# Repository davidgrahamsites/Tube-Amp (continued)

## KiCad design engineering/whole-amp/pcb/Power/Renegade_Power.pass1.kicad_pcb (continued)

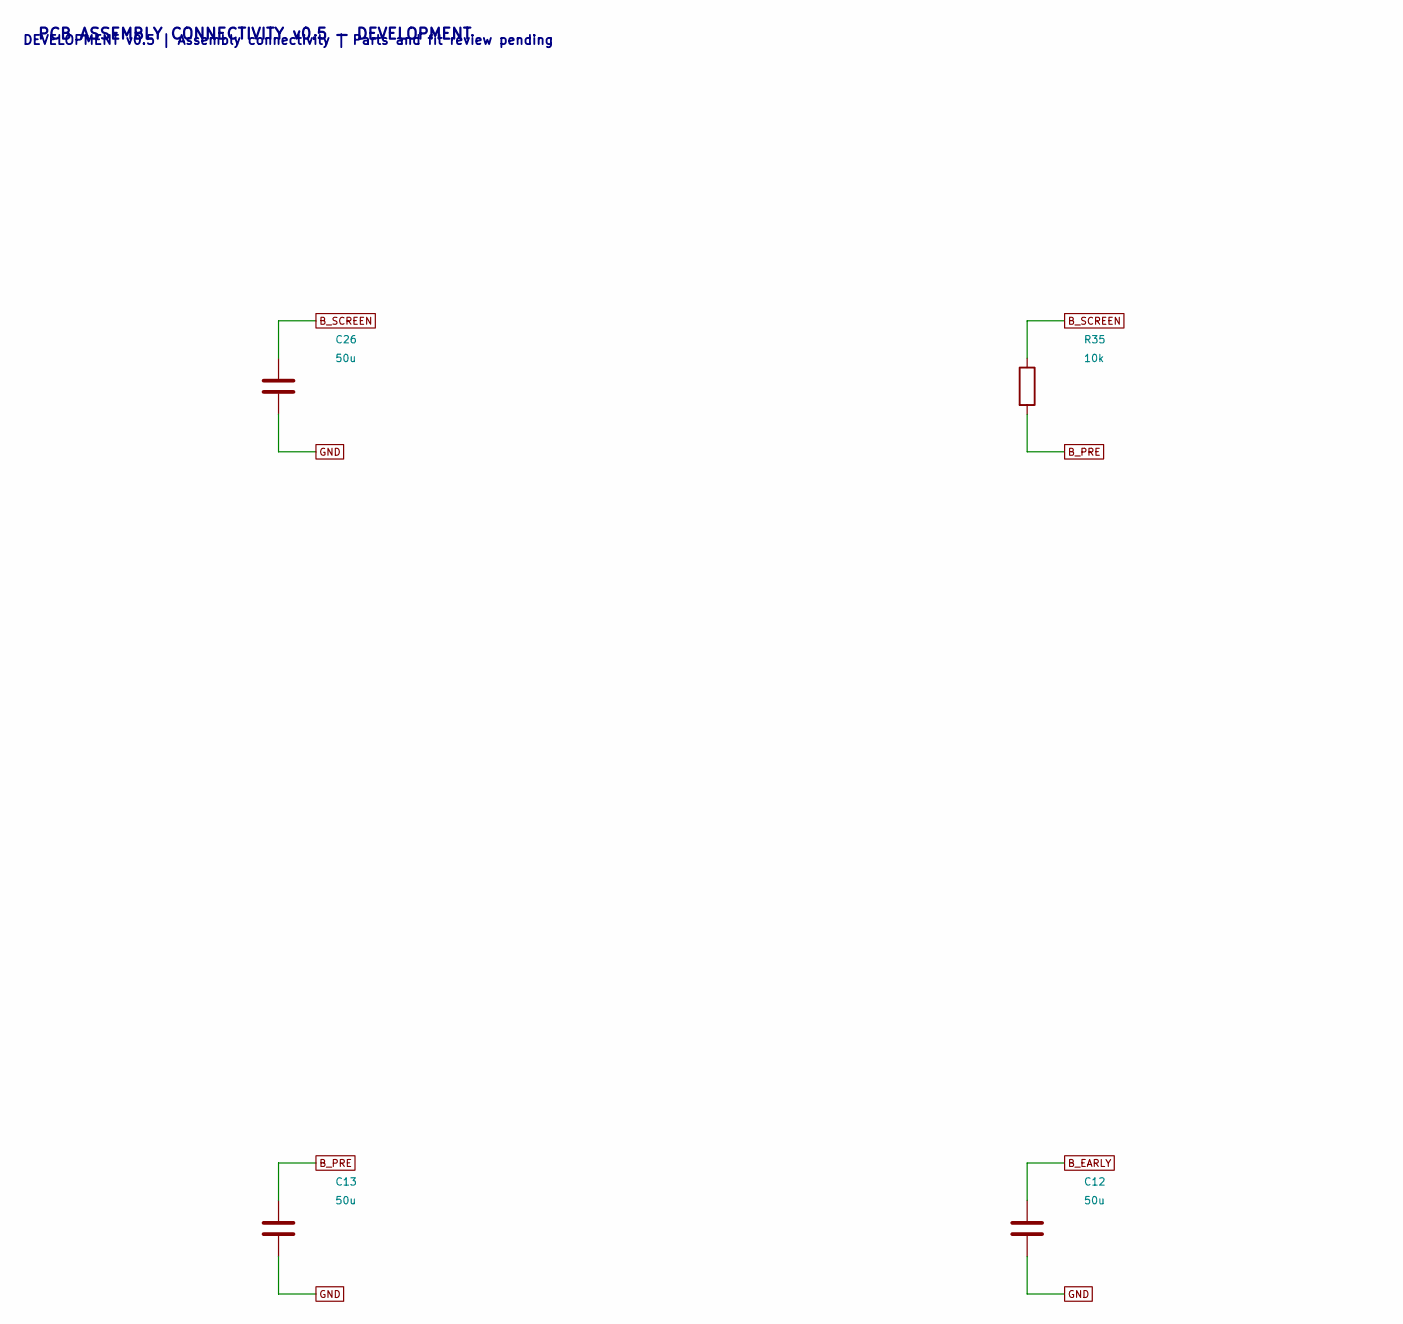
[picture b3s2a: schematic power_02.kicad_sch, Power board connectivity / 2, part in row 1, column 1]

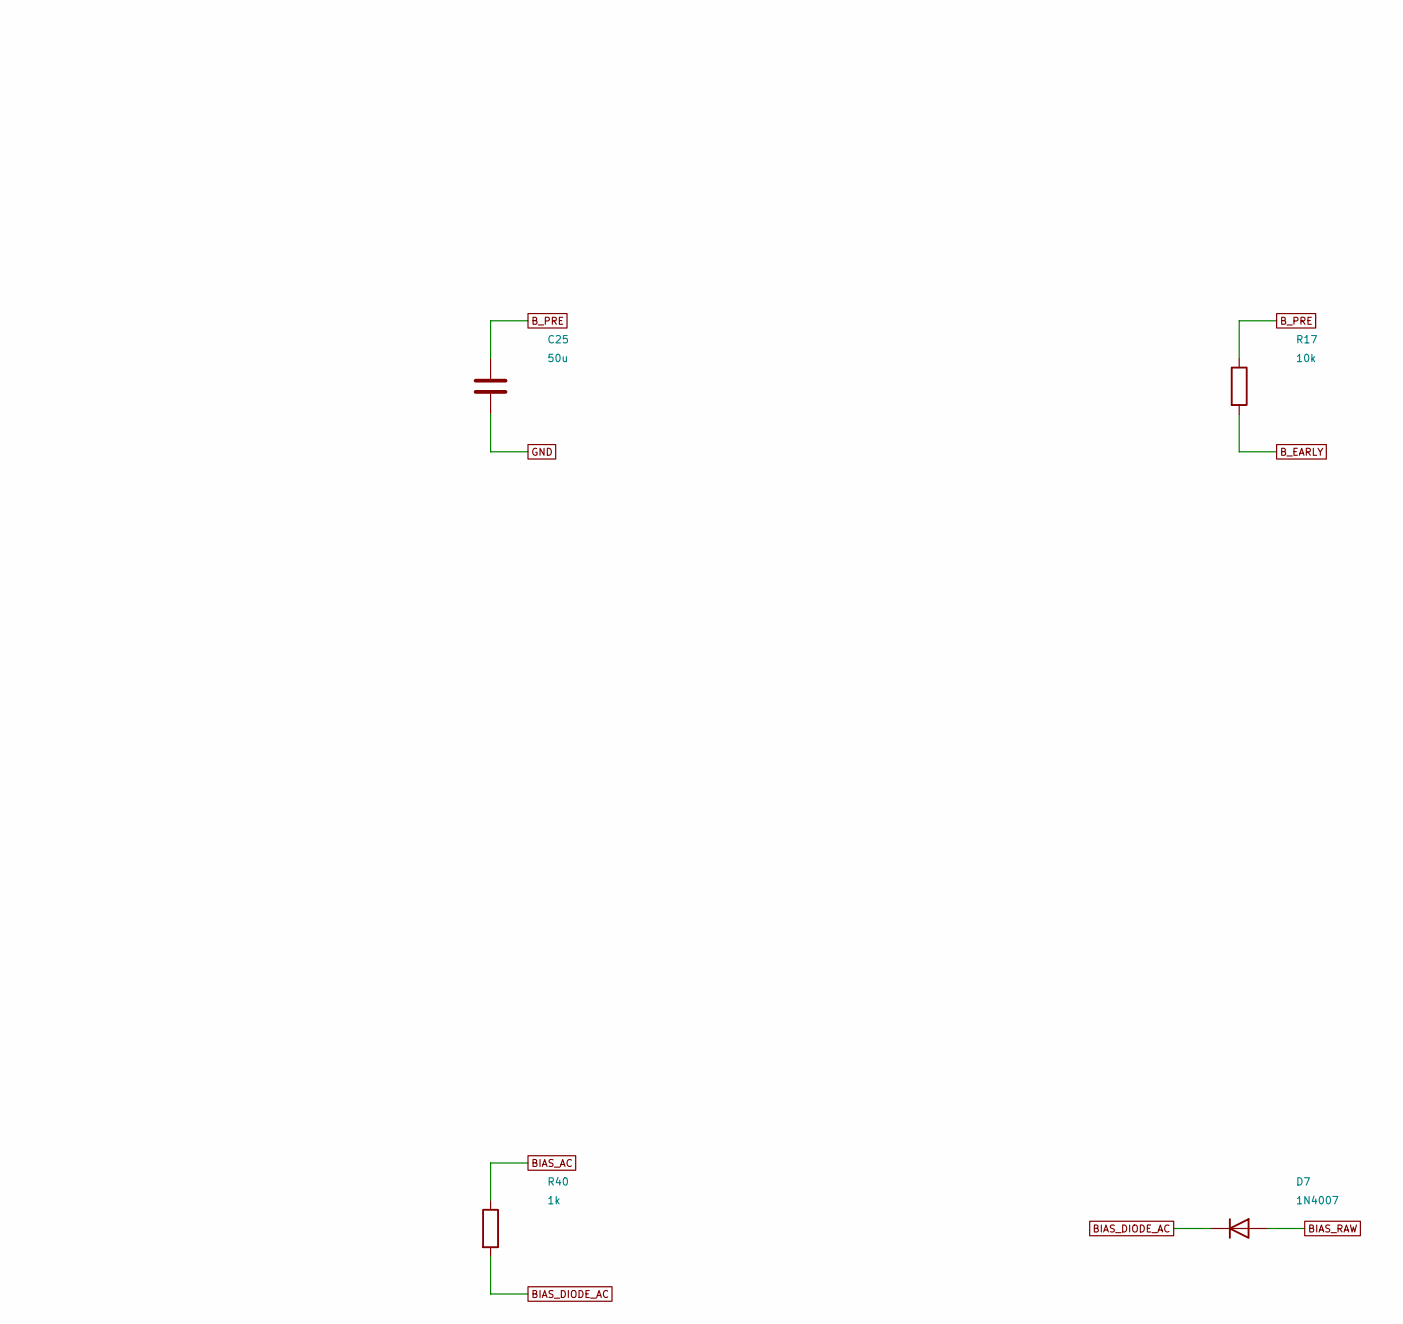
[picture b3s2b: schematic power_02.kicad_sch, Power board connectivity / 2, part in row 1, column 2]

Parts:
C12, C13, C25, C26: 50u; Panasonic_EZPV60506MTC; Rating 50uF 600VDC film; official RDL0000C251 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
D7: 1N4007; D_DO-41_SOD81_P10.16mm_Horizontal
R17, R35: 10k; R_Axial_DIN0414_L11.9mm_D4.5mm_P15.24mm_Horizontal; Rating 5 W
R40: 1k; R_Axial_DIN0207_L6.3mm_D2.5mm_P15.24mm_Horizontal; Rating 1 W

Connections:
BIAS_AC: R40.1; also elsewhere on the board
BIAS_DIODE_AC: D7.1 (K), R40.2
BIAS_RAW: D7.2 (A); also elsewhere on the board
B_EARLY: C12.1, R17.2; also elsewhere on the board
B_PRE: C13.1, C25.1, R17.1, R35.2; also elsewhere on the board
B_SCREEN: C26.1, R35.1; also elsewhere on the board
GND: C12.2, C13.2, C25.2, C26.2; also elsewhere on the board

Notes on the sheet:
PCB ASSEMBLY CONNECTIVITY v0.5 — DEVELOPMENT
DEVELOPMENT v0.5 | Assembly connectivity | Parts and fit review pending

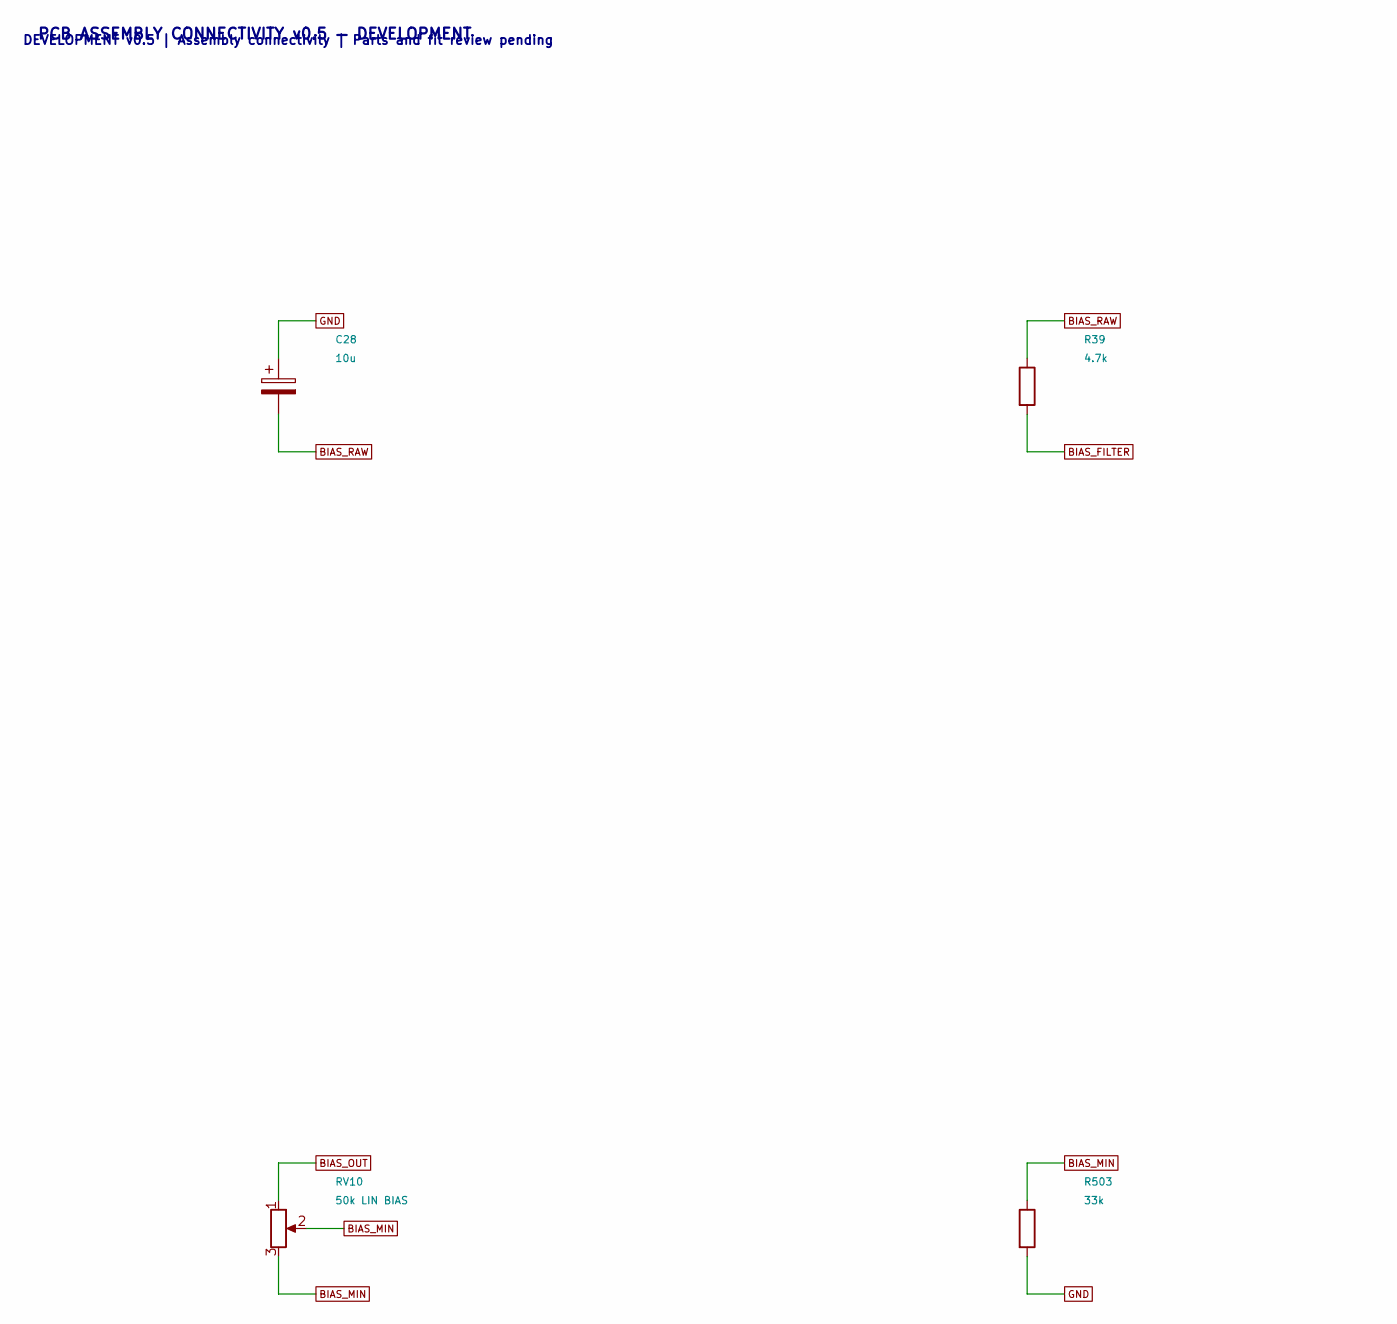
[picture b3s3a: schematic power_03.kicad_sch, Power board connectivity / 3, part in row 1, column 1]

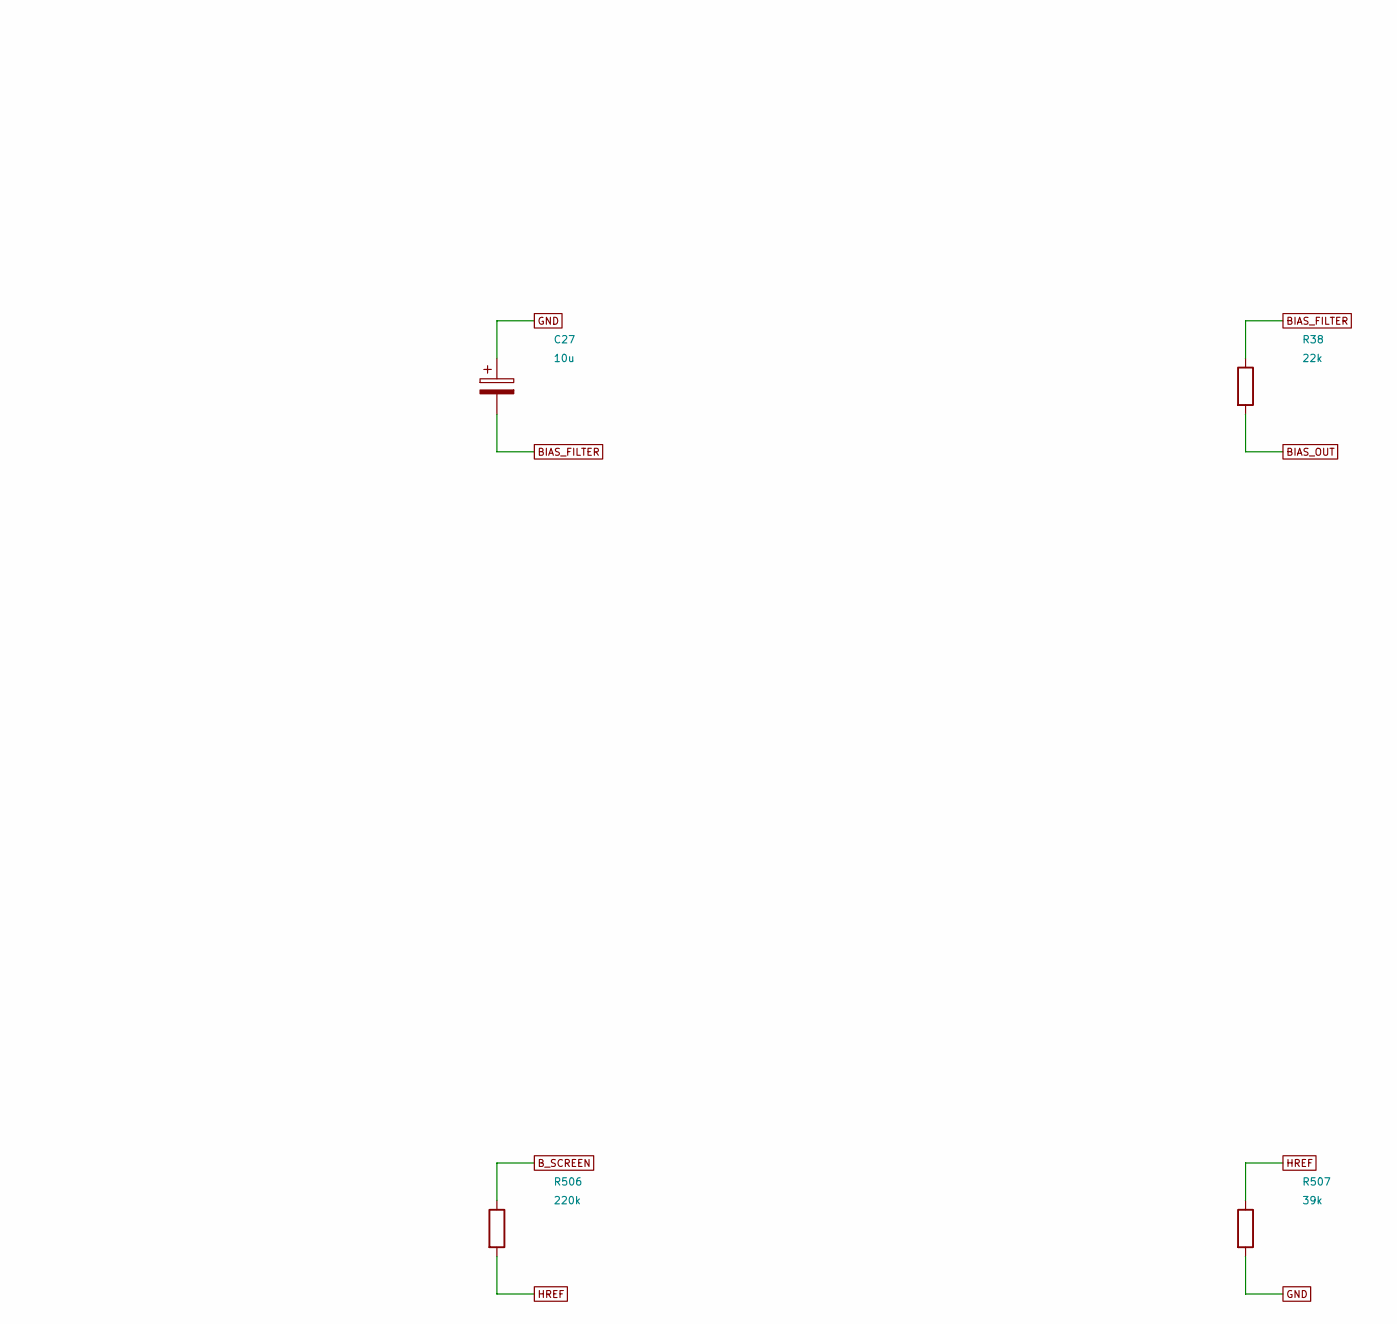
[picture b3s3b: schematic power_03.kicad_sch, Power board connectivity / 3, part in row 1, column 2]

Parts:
C27, C28: 10u; CP_Radial_D10.0mm_P5.00mm; Rating 100 V
R38: 22k; R_Axial_DIN0207_L6.3mm_D2.5mm_P15.24mm_Horizontal; Rating 1 W
R39: 4.7k; R_Axial_DIN0207_L6.3mm_D2.5mm_P15.24mm_Horizontal; Rating 1 W
R503: 33k; R_Axial_DIN0207_L6.3mm_D2.5mm_P15.24mm_Horizontal; Rating 1 W; minimum negative-bias stop
R506: 220k; R_Axial_DIN0414_L11.9mm_D4.5mm_P15.24mm_Horizontal; Rating 2 W; voltage rating pending
R507: 39k; R_Axial_DIN0207_L6.3mm_D2.5mm_P15.24mm_Horizontal; Rating 1 W
RV10: 50k LIN BIAS; Potentiometer_Bourns_3296W_Vertical; Rating Off-board; voltage, taper and drawing r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

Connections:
BIAS_FILTER: C27.2, R38.1, R39.2
BIAS_MIN: R503.1, RV10.2, RV10.3
BIAS_OUT: R38.2, RV10.1; also elsewhere on the board
BIAS_RAW: C28.2, R39.1; also elsewhere on the board
B_SCREEN: R506.1; also elsewhere on the board
GND: C27.1, C28.1, R503.2, R507.2; also elsewhere on the board
HREF: R506.2, R507.1; also elsewhere on the board

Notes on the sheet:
PCB ASSEMBLY CONNECTIVITY v0.5 — DEVELOPMENT
DEVELOPMENT v0.5 | Assembly connectivity | Parts and fit review pending

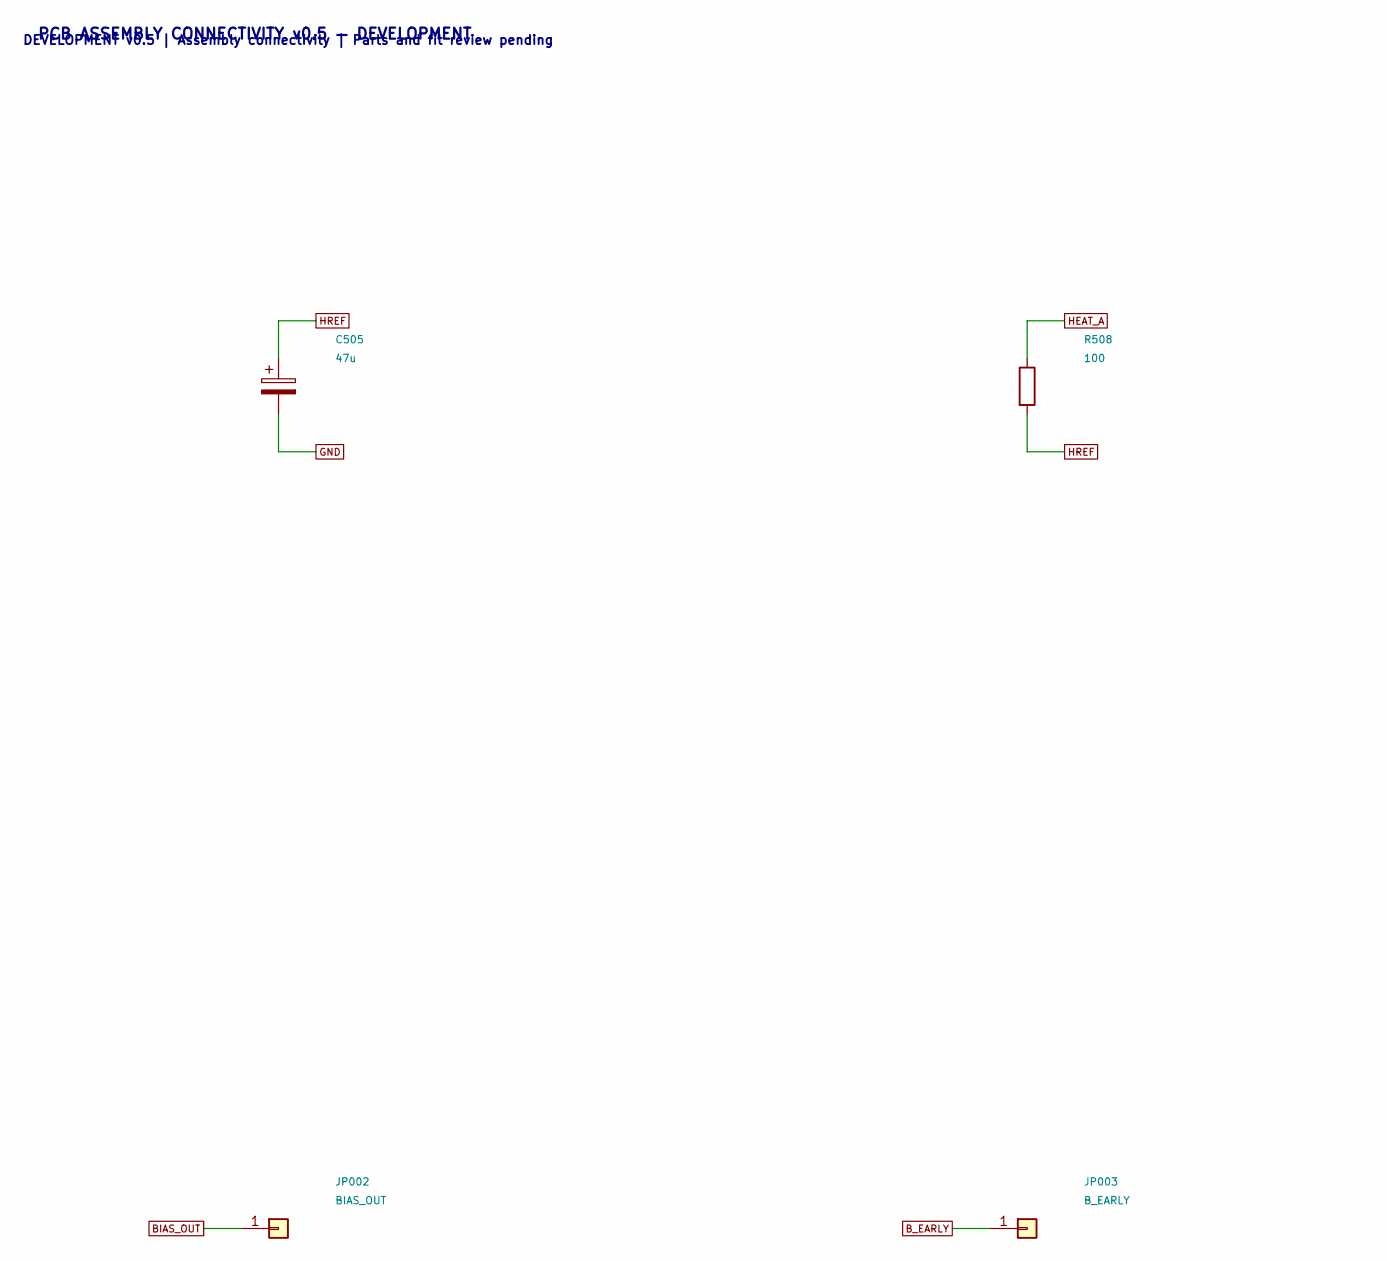
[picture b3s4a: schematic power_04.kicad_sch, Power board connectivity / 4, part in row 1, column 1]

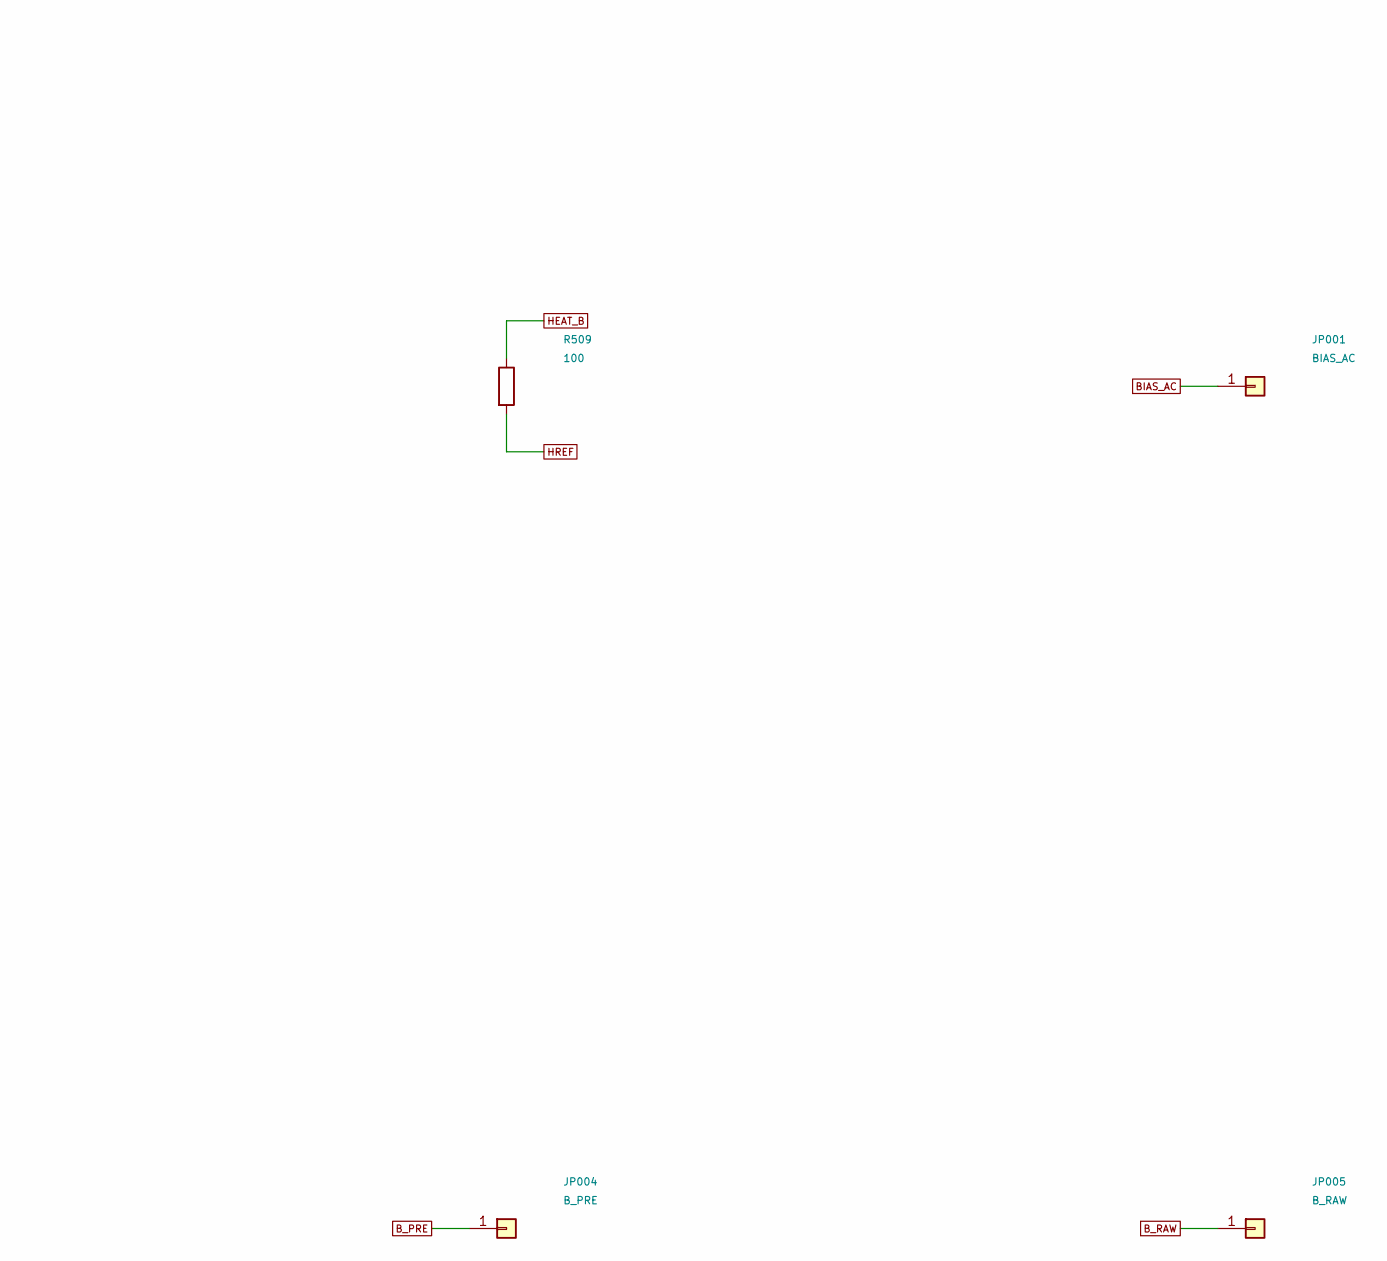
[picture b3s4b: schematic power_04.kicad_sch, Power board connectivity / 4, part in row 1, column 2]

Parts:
C505: 47u; CP_Radial_D10.0mm_P5.00mm; Rating 160 V
JP001: BIAS_AC; WirePad_1.3mm; Rating Soldered and strain-relieved wire, volt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
JP002: BIAS_OUT; WirePad_1.3mm; Rating Soldered and strain-relieved wire, volt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
JP003: B_EARLY; WirePad_1.3mm; Rating Soldered and strain-relieved wire, volt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
JP004: B_PRE; WirePad_1.3mm; Rating Soldered and strain-relieved wire, volt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
JP005: B_RAW; WirePad_1.3mm; Rating Soldered and strain-relieved wire, volt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
R508, R509: 100; R_Axial_DIN0207_L6.3mm_D2.5mm_P15.24mm_Horizontal; Rating 0.5 W

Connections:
BIAS_AC: JP001.1; also elsewhere on the board
BIAS_OUT: JP002.1; also elsewhere on the board
B_EARLY: JP003.1; also elsewhere on the board
B_PRE: JP004.1; also elsewhere on the board
B_RAW: JP005.1; also elsewhere on the board
GND: C505.2; also elsewhere on the board
HEAT_A: R508.1; also elsewhere on the board
HEAT_B: R509.1; also elsewhere on the board
HREF: C505.1, R508.2, R509.2; also elsewhere on the board

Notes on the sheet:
PCB ASSEMBLY CONNECTIVITY v0.5 — DEVELOPMENT
DEVELOPMENT v0.5 | Assembly connectivity | Parts and fit review pending

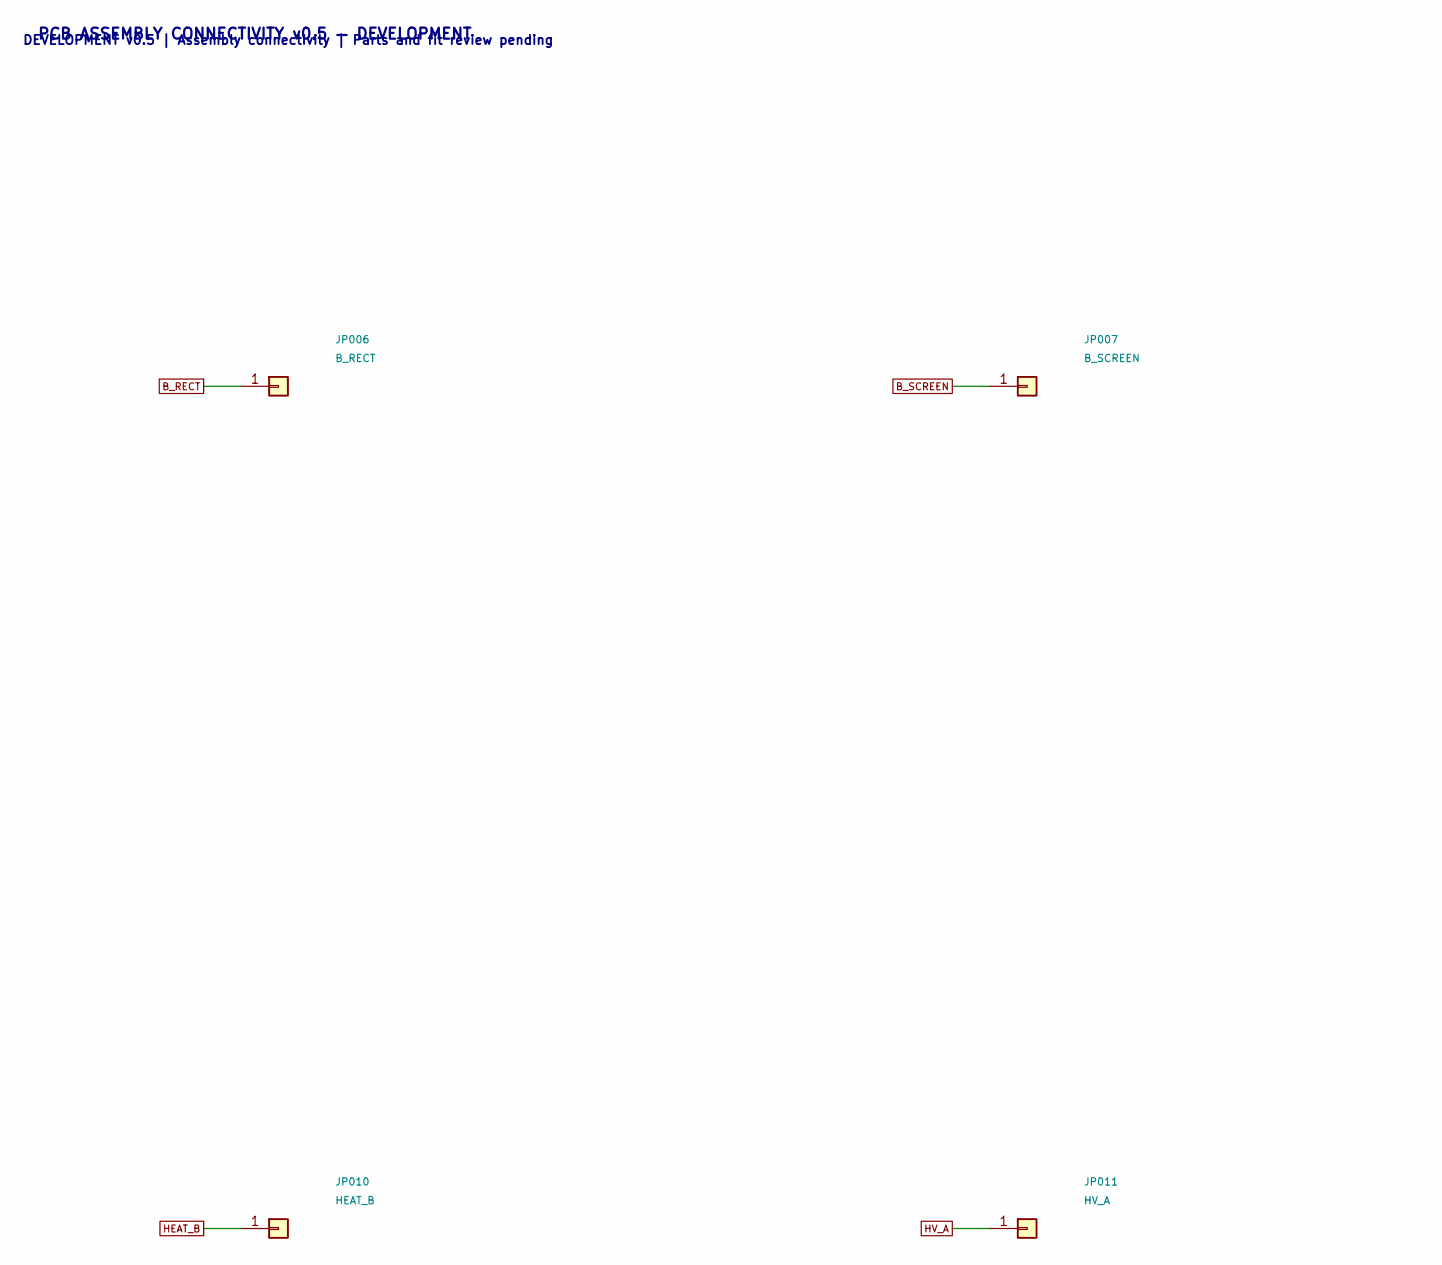
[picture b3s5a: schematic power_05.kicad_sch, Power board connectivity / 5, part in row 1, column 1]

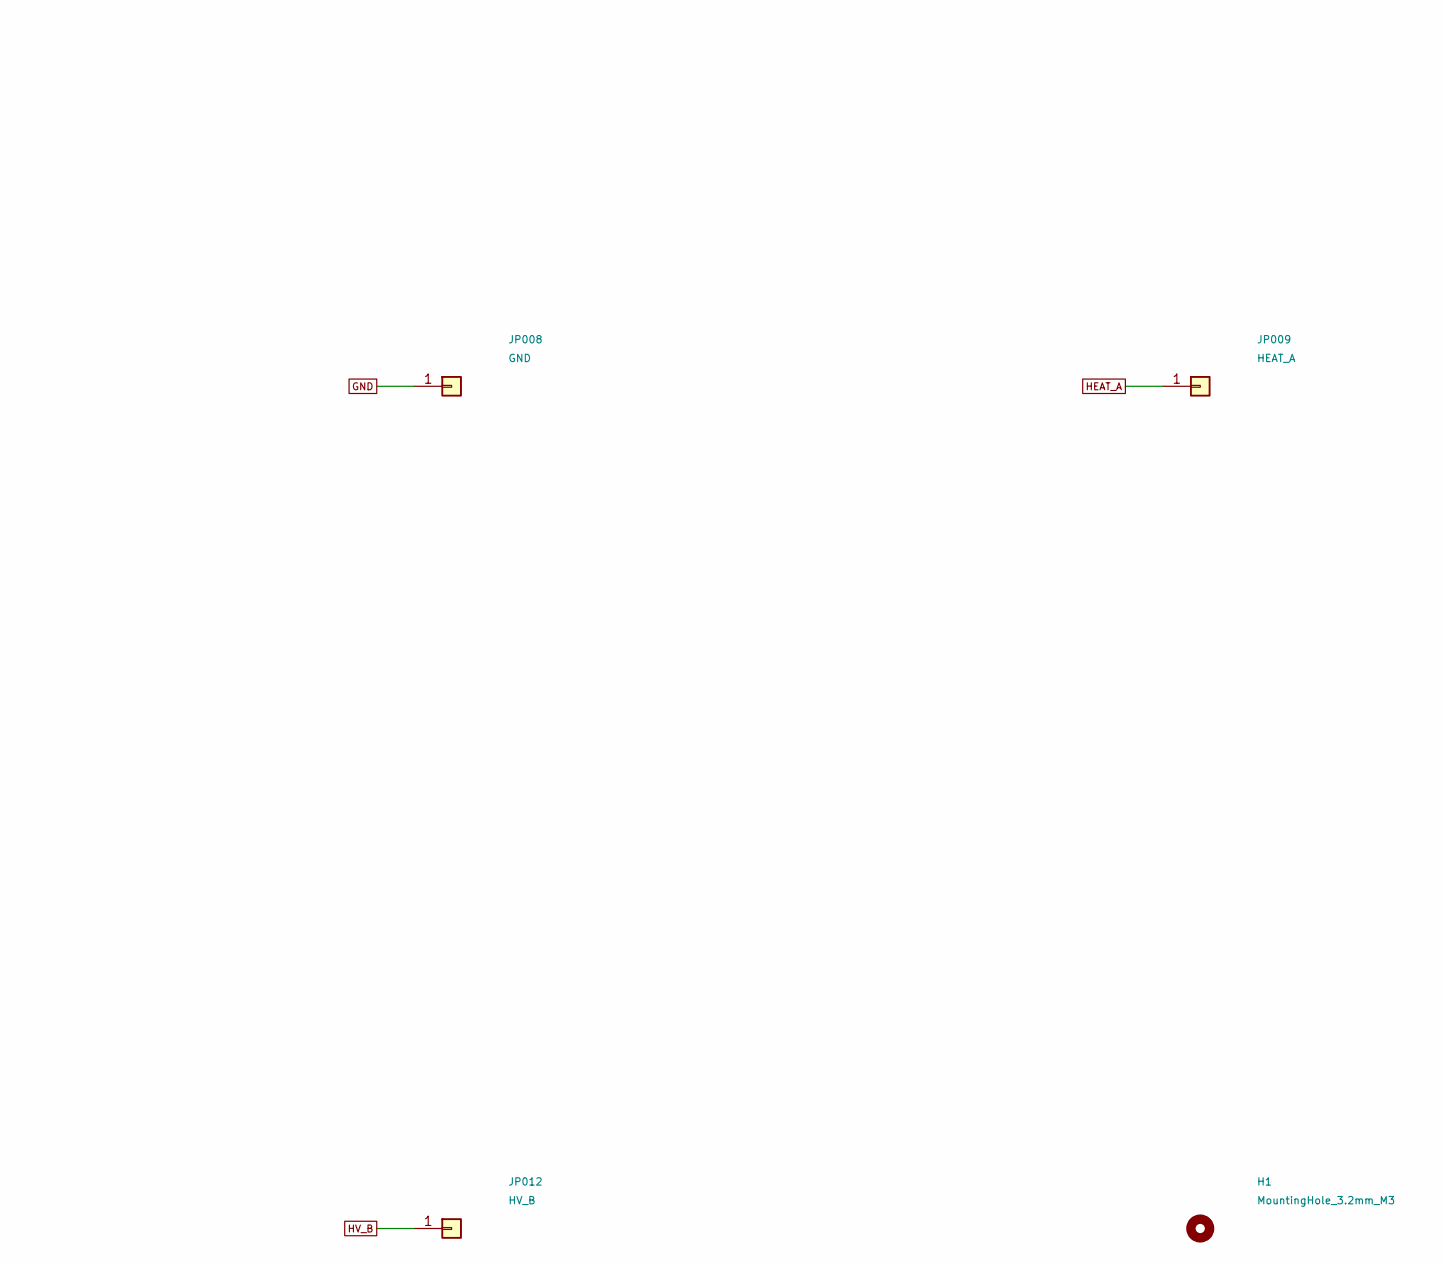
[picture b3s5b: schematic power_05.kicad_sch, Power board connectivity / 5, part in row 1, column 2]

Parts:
H1: MountingHole_3.2mm_M3
JP006: B_RECT; WirePad_1.3mm; Rating Soldered and strain-relieved wire, volt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
JP007: B_SCREEN; WirePad_1.3mm; Rating Soldered and strain-relieved wire, volt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
JP008: GND; WirePad_1.3mm; Rating Soldered and strain-relieved wire, volt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
JP009: HEAT_A; WirePad_1.3mm; Rating Soldered and strain-relieved wire, volt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
JP010: HEAT_B; WirePad_1.3mm; Rating Soldered and strain-relieved wire, volt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
JP011: HV_A; WirePad_1.3mm; Rating Soldered and strain-relieved wire, volt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
JP012: HV_B; WirePad_1.3mm; Rating Soldered and strain-relieved wire, volt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

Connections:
B_RECT: JP006.1; also elsewhere on the board
B_SCREEN: JP007.1; also elsewhere on the board
GND: JP008.1; also elsewhere on the board
HEAT_A: JP009.1; also elsewhere on the board
HEAT_B: JP010.1; also elsewhere on the board
HV_A: JP011.1; also elsewhere on the board
HV_B: JP012.1; also elsewhere on the board

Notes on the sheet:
PCB ASSEMBLY CONNECTIVITY v0.5 — DEVELOPMENT
DEVELOPMENT v0.5 | Assembly connectivity | Parts and fit review pending

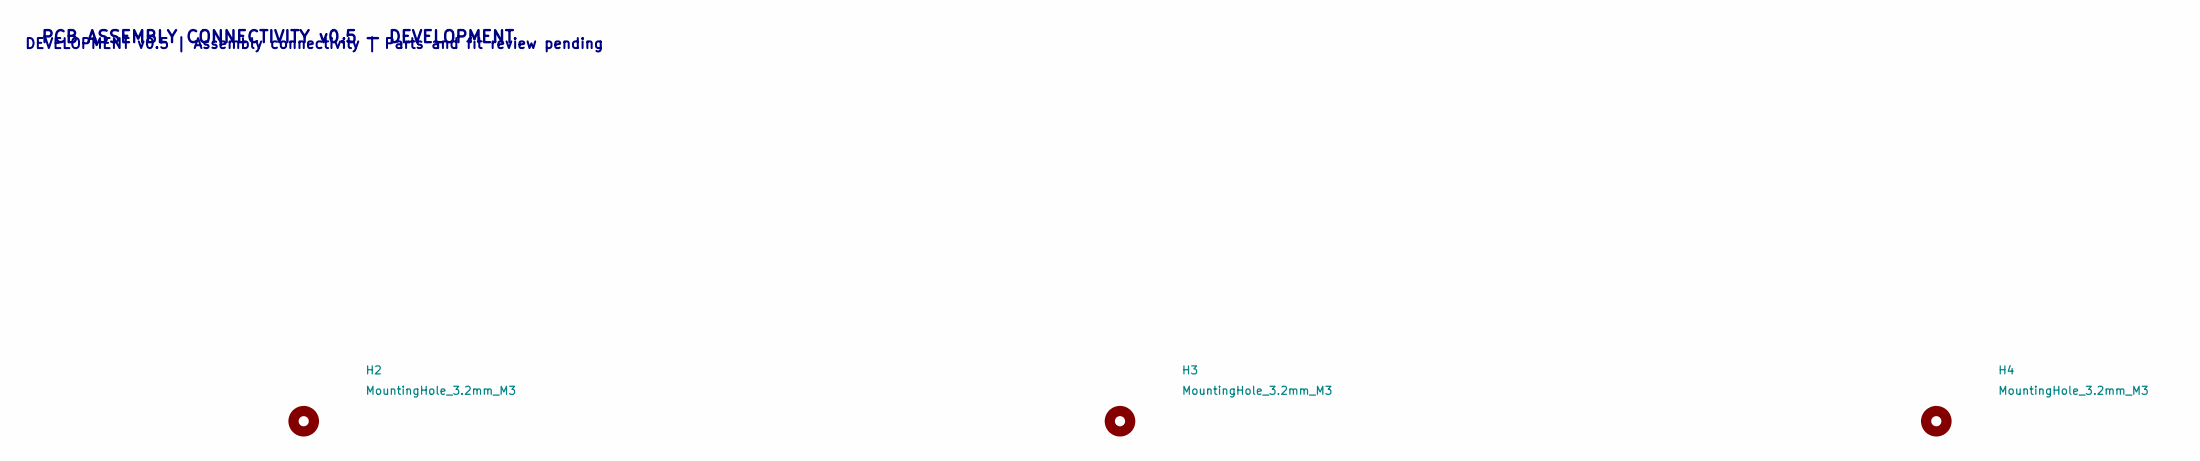
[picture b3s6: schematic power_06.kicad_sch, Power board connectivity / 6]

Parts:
H2, H3, H4: MountingHole_3.2mm_M3

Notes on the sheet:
PCB ASSEMBLY CONNECTIVITY v0.5 — DEVELOPMENT
DEVELOPMENT v0.5 | Assembly connectivity | Parts and fit review pending

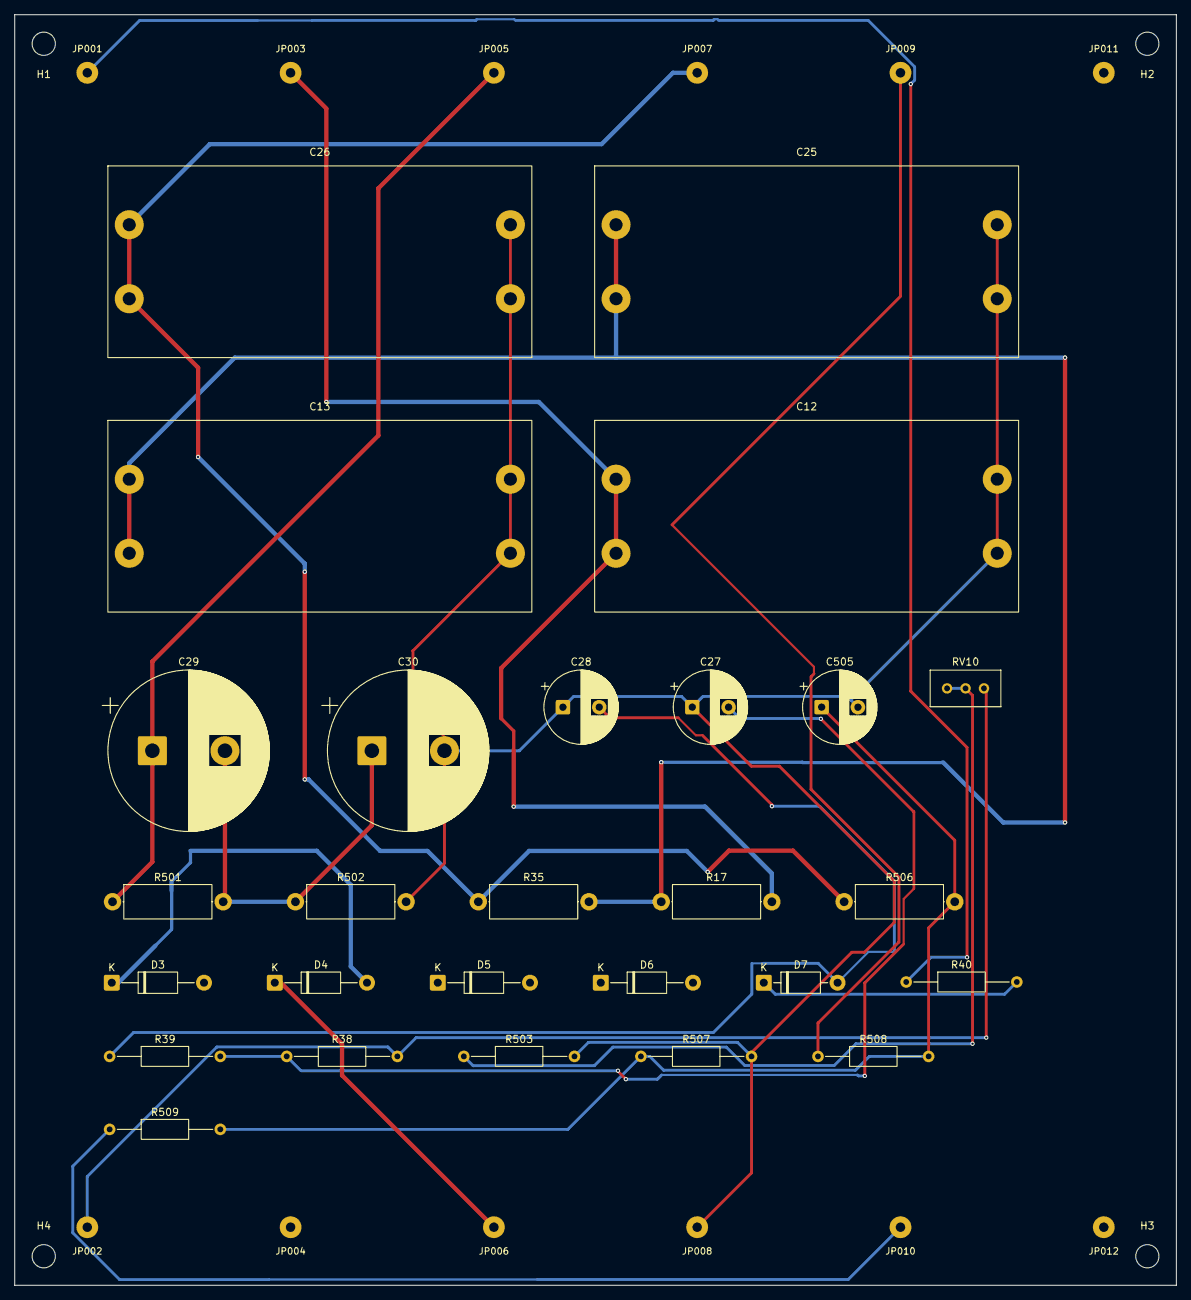
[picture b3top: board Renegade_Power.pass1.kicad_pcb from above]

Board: 2 copper layers, 160.0 x 175.0 mm, 43 parts (0 on the bottom side), 20 nets.

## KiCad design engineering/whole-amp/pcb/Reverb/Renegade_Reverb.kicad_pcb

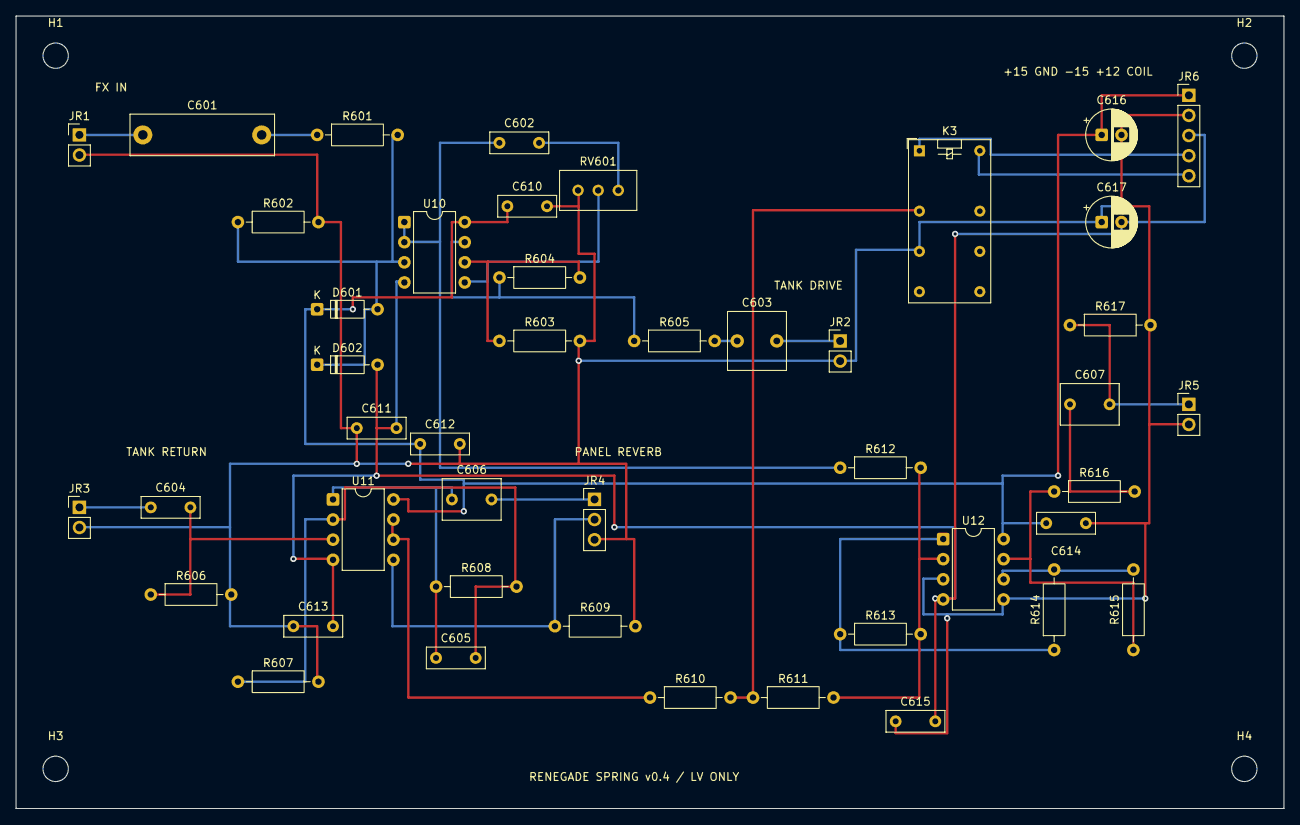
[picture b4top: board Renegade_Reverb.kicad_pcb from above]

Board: 2 copper layers, 160.0 x 100.0 mm, 49 parts (0 on the bottom side), 29 nets.

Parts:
C601: 100n; C_Rect_L18.0mm_W5.0mm_P15.00mm_FKS3_FKP3
C602: 22n; C_Rect_L7.2mm_W2.5mm_P5.00mm
C603: 2.2u; C_Rect_L7.2mm_W7.2mm_P5.00mm
C604, C610, C611, C612, C613, C614, C615: 100n; C_Rect_L7.2mm_W2.5mm_P5.00mm
C605: 330p; C_Rect_L7.2mm_W2.5mm_P5.00mm
C606, C607: 1u; C_Rect_L7.2mm_W5.0mm_P5.00mm
C616, C617: 47u; CP_Radial_D6.3mm_P2.50mm
D601, D602: 1N4148; D_DO-35_SOD27_P7.62mm_Horizontal
H1, H2, H3, H4: MountingHole_3.2mm_M3
JR1: JR1 harness; PinHeader_1x02_P2.54mm_Vertical
JR2: JR2 harness; PinHeader_1x02_P2.54mm_Vertical
JR3: JR3 harness; PinHeader_1x02_P2.54mm_Vertical
JR4: JR4 harness; PinHeader_1x03_P2.54mm_Vertical
JR5: JR5 harness; PinHeader_1x02_P2.54mm_Vertical
JR6: JR6 harness; PinHeader_1x05_P2.54mm_Vertical
K3: G5V-2-H1 DC12; Relay_DPDT_Omron_G5V-2
R601, R608, R611, R612, R613, R614, R615: 100k; R_Axial_DIN0207_L6.3mm_D2.5mm_P10.16mm_Horizontal
R602: 10M; R_Axial_DIN0207_L6.3mm_D2.5mm_P10.16mm_Horizontal
R603, R604, R610: 10k; R_Axial_DIN0207_L6.3mm_D2.5mm_P10.16mm_Horizontal
R605: 220; R_Axial_DIN0207_L6.3mm_D2.5mm_P10.16mm_Horizontal
R606: 220k; R_Axial_DIN0207_L6.3mm_D2.5mm_P10.16mm_Horizontal
R607: 1k; R_Axial_DIN0207_L6.3mm_D2.5mm_P10.16mm_Horizontal
R609, R617: 1M; R_Axial_DIN0207_L6.3mm_D2.5mm_P10.16mm_Horizontal
R616: 100; R_Axial_DIN0207_L6.3mm_D2.5mm_P10.16mm_Horizontal
RV601: 100k SEND trim; Potentiometer_Bourns_3296W_Vertical
U10, U11, U12: OPA2134PA; DIP-8_W7.62mm

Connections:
+12V: JR6.4, K3.1
+15V: C610.1, C612.1, C614.1, C616.1, D601.1, JR6.1, U10.8, U11.8, U12.8
-15V: C611.2, C613.2, C615.2, C617.2, D602.2, JR6.3, U10.4, U11.4, U12.4
COIL_REV: JR6.5, K3.16
DRY_BUF: C602.1, R612.1, U10.1, U10.2
FX_RETURN: C601.1, JR1.1
GND: C610.2, C611.1, C612.2, C613.1, C614.2, C615.1, C616.2, C617.1, JR1.2, JR2.2, JR3.2, JR4.3, JR5.2, JR6.2, K3.6, R602.2, R603.2, R606.2, R607.2, R609.2, R617.2, RV601.3, U12.3, U12.5
MIX_OUT: C607.2, JR5.1, R617.1
unnamed: C601.2, R601.1
unnamed: C602.2, RV601.1
unnamed: C603.1, R605.2
unnamed: C605.1, C606.1, R608.1, U11.1
unnamed: C607.1, R616.2
unnamed: D601.2, D602.1, R601.2, R602.1, U10.3
unnamed: K3.4, R610.2, R611.1
unnamed: R604.1, R605.1, U10.7
unnamed: R615.1, R616.1, U12.7
unnamed: RV601.2, U10.5
unnamed: R603.1, R604.2, U10.6
unnamed: C604.2, R606.1, U11.3
unnamed: C605.2, R607.1, R608.2, U11.2
unnamed: R610.1, U11.6, U11.7
unnamed: R611.2, R612.2, R613.2, U12.2
unnamed: R614.2, R615.2, U12.6
SUM_INV: R613.1, R614.1, U12.1
TANK_IN: C603.2, JR2.1
TANK_OUT: C604.1, JR3.1
WET_TOP: C606.2, JR4.1
WET_W: JR4.2, R609.1, U11.5
